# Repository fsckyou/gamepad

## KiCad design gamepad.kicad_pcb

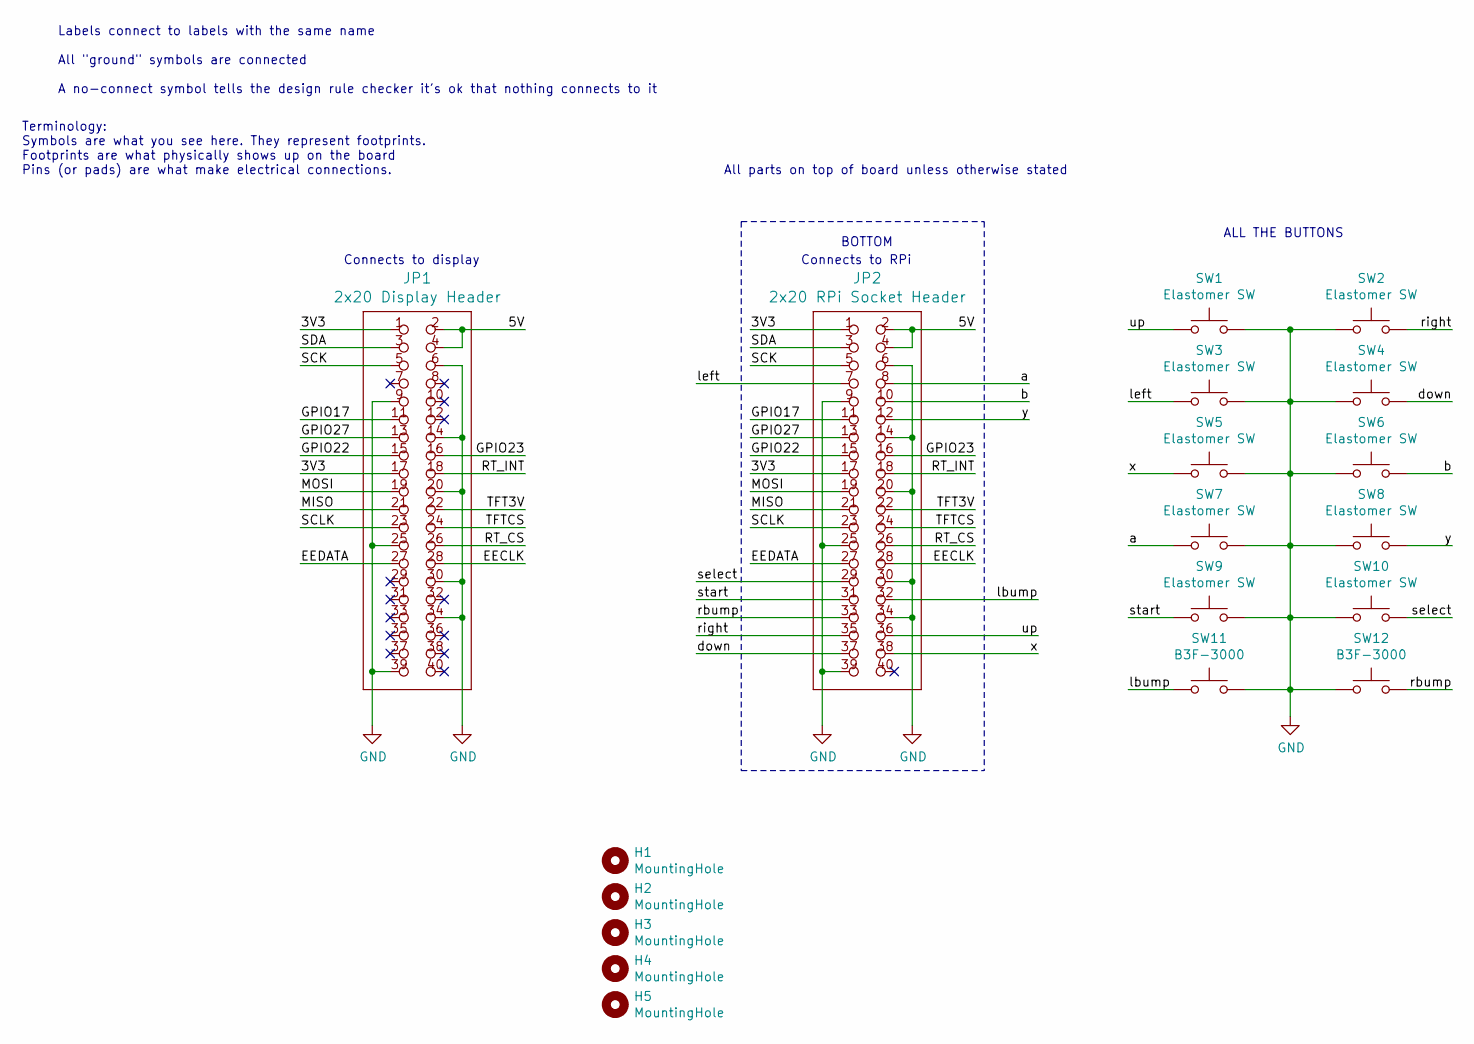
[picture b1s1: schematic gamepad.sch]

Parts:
H1, H2, H3, H4, H5: MountingHole; MountingHole_2.7mm_M2.5
JP1: 2x20 Display Header; PinHeader_2x20_P2.54mm_Vertical
JP2: 2x20 RPi Socket Header; PinSocket_2x20_P2.54mm_Vertical
SW1, SW2, SW3, SW4, SW5, SW6, SW7, SW8, SW9, SW10: Elastomer SW; 8mm_elastomer_button
SW11, SW12: B3F-3000

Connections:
/3V3: JP1.1, JP1.17, JP2.1, JP2.17
/5V: JP1.2, JP1.4, JP2.2, JP2.4
/EECLK: JP1.28, JP2.28
/EEDATA: JP1.27, JP2.27
/GPIO17: JP1.11, JP2.11
/GPIO22: JP1.15, JP2.15
/GPIO23: JP1.16, JP2.16
/GPIO27: JP1.13, JP2.13
/MISO: JP1.21, JP2.21
/MOSI: JP1.19, JP2.19
/RT_CS: JP1.26, JP2.26
/RT_INT: JP1.18, JP2.18
/SCK: JP1.5, JP2.5
/SCLK: JP1.23, JP2.23
/SDA: JP1.3, JP2.3
/TFT3V: JP1.22, JP2.22
/TFTCS: JP1.24, JP2.24
/a: JP2.8, SW7.1
/b: JP2.10, SW6.2
/down: JP2.37, SW4.2
/lbump: JP2.32, SW11.1
/left: JP2.7, SW3.1
/rbump: JP2.33, SW12.2
/right: JP2.35, SW2.2
/select: JP2.29, SW10.2
/start: JP2.31, SW9.1
/up: JP2.36, SW1.1
/x: JP2.38, SW5.1
/y: JP2.12, SW8.2
GND: JP1.6, JP1.9, JP1.14, JP1.20, JP1.25, JP1.30, JP1.34, JP1.39, JP2.6, JP2.9, JP2.14, JP2.20, JP2.25, JP2.30, JP2.34, JP2.39, SW1.2, SW2.1, SW3.2, SW4.1, SW5.2, SW6.1, SW7.2, SW8.1, SW9.2, SW10.1, SW11.2, SW12.1

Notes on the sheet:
BOTTOM
All parts on top of board unless otherwise stated
Connects to RPi
Connects to display
ALL THE BUTTONS
Labels connect to labels with the same name All "ground" symbols are connected A no-connect symbol tells the design rule checker it's ok that nothing connects to it
Terminology: Symbols are what you see here. They represent footprints. Footprints are what physically shows up on the board Pins (or pads) are what make electrical connections.

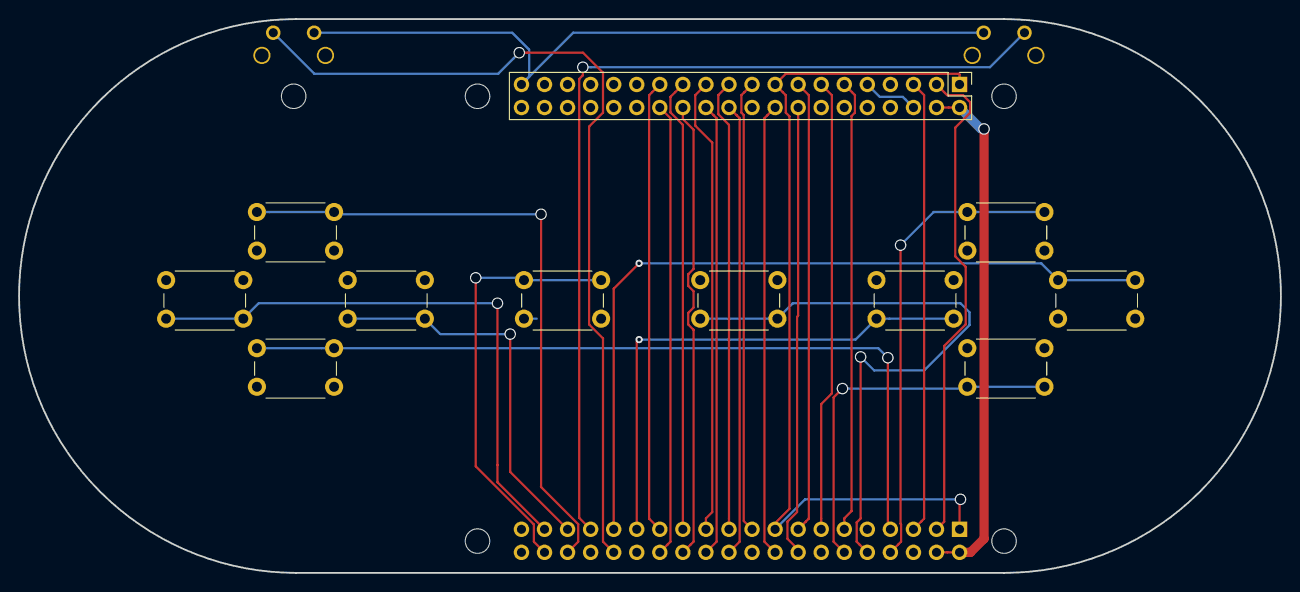
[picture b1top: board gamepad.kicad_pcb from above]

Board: 2 copper layers, 139.0 x 61.0 mm, 19 parts (0 on the bottom side), 30 nets.

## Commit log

2019-10-25 my project as it is
2019-10-26 finished layout
2019-10-26 fixed oopsy whoopsy
2019-10-26 finally saved again
2019-11-02 Finalized Rev B
